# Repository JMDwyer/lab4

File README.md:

# Lab 4: Final Project for ECE 3150
## Team Members: Peter Slater (pas324), Elise Weir (enw23), Joseph Dwyer (jmd456)

### Project Proposal:
>https://docs.google.com/a/cornell.edu/document/d/10tSfkiGi9rwJxMmEFkQvBJDazQcpqDf9e9OWjNXq8RM/edit?usp=sharing

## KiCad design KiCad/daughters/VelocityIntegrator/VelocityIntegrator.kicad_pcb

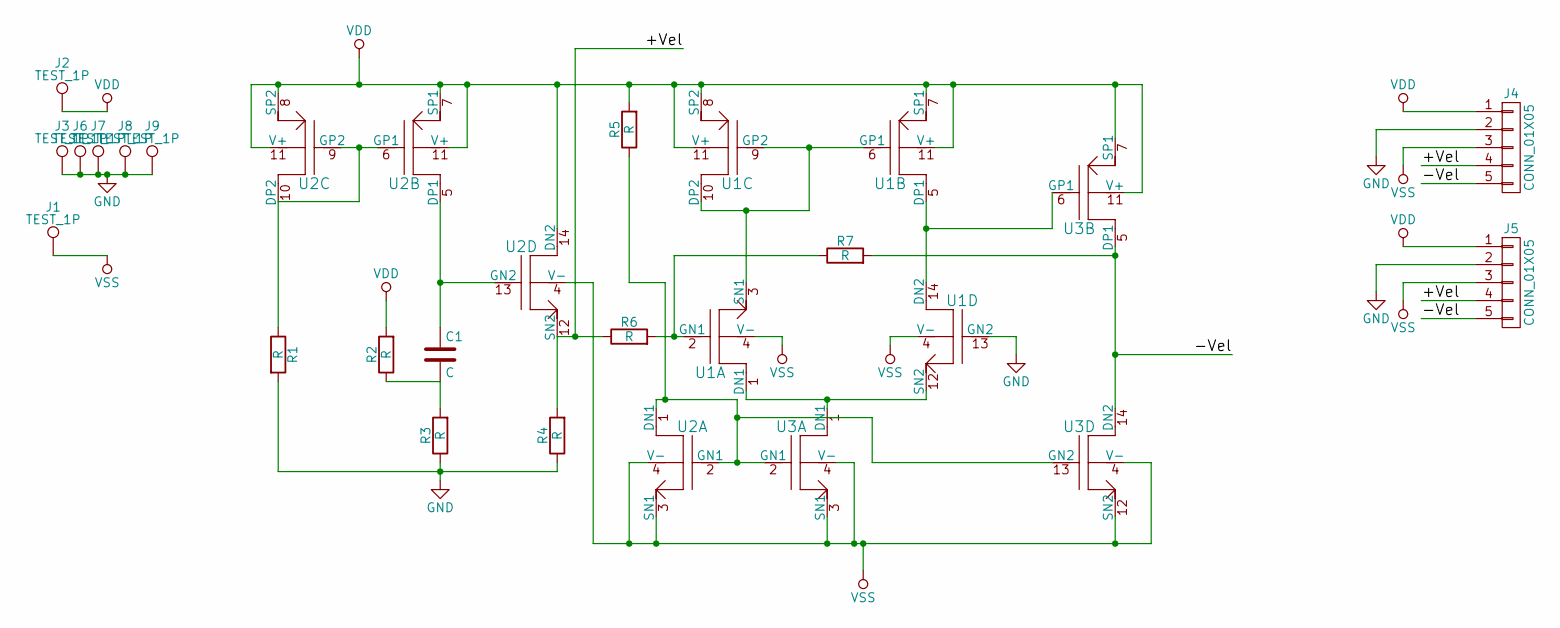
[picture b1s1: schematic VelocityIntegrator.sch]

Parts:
C1: C; CP_Radial_D10.0mm_P5.00mm
J1, J2, J3, J6, J7, J8, J9: TEST_1P; Test_Point
J4, J5: CONN_01X05; Pin_Header_Straight_1x05_Pitch2.54mm
R1, R2, R3, R4, R5, R6, R7: R; R_Axial_DIN0204_L3.6mm_D1.6mm_P5.08mm_Vertical
U1, U2, U3: ALD1105; DIP-14_W7.62mm_LongPads

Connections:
/+Vel: J4.4, J5.4, R4.2, R6.1, U2.12 (SN2)
/-Vel: J4.5, J5.5, R7.2, U3.5 (DP1), U3.14 (DN2)
GND: J3.1, J4.2, J5.2, J6.1, J7.1, J8.1, J9.1, R1.2, R3.1, R4.1, U1.13 (GN2)
unnamed: C1.1, U2.5 (DP1), U2.13 (GN2)
unnamed: C1.2, R2.1, R3.2
unnamed: R1.1, U2.6 (GP1), U2.9 (GP2), U2.10 (DP2)
unnamed: R5.1, U2.1 (DN1), U2.2 (GN1), U3.2 (GN1), U3.13 (GN2)
unnamed: R6.2, R7.1, U1.2 (GN1)
unnamed: U1.1 (DN1), U1.12 (SN2), U3.1 (DN1)
unnamed: U1.3 (SN1), U1.6 (GP1), U1.9 (GP2), U1.10 (DP2)
unnamed: U1.5 (DP1), U1.14 (DN2), U3.6 (GP1)
VDD: J2.1, J4.1, J5.1, R2.2, R5.2, U1.7 (SP1), U1.8 (SP2), U1.11 (V+), U2.7 (SP1), U2.8 (SP2), U2.11 (V+), U2.14 (DN2), U3.7 (SP1), U3.11 (V+)
VSS: J1.1, J4.3, J5.3, U1.4 (V-), U2.3 (SN1), U2.4 (V-), U3.3 (SN1), U3.4 (V-), U3.12 (SN2)

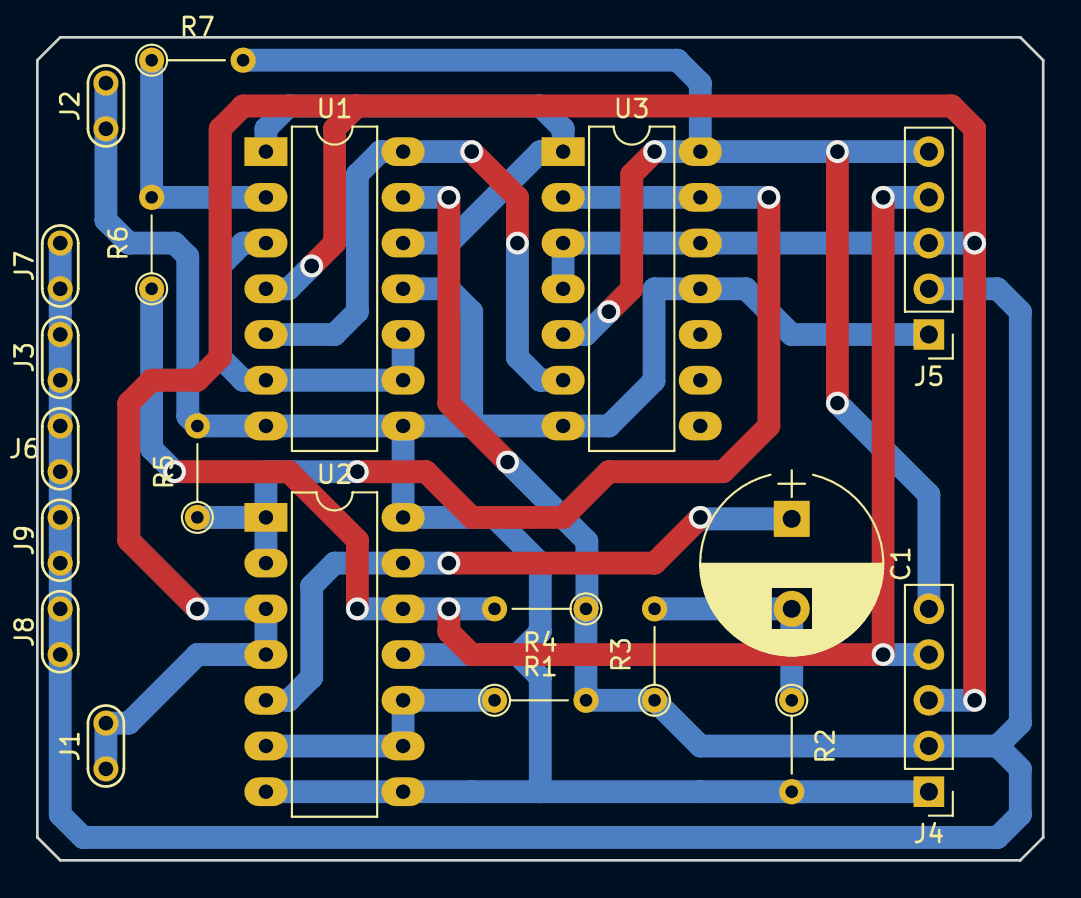
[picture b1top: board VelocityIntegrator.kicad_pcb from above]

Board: 2 copper layers, 55.9 x 45.7 mm, 20 parts (0 on the bottom side), 13 nets.

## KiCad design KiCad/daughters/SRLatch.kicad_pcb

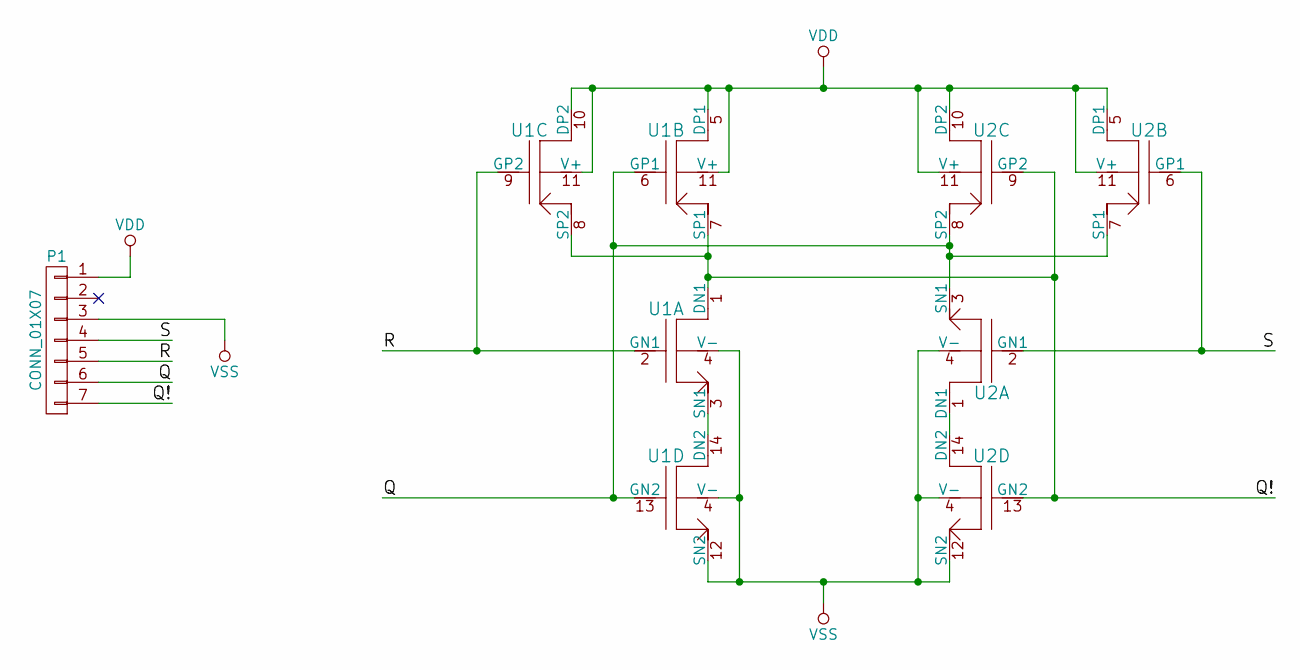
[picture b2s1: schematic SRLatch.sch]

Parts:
P1: CONN_01X07; Pin_Header_Straight_1x07_Pitch2.54mm
U1, U2: ALD1105; DIP-14_W7.62mm_LongPads

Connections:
/Q: P1.6, U1.6 (GP1), U1.13 (GN2), U2.3 (SN1), U2.7 (SP1), U2.8 (SP2)
/Q!: P1.7, U1.1 (DN1), U1.7 (SP1), U1.8 (SP2), U2.9 (GP2), U2.13 (GN2)
/R: P1.5, U1.2 (GN1), U1.9 (GP2)
/S: P1.4, U2.2 (GN1), U2.6 (GP1)
unnamed: U1.3 (SN1), U1.14 (DN2)
unnamed: U2.1 (DN1), U2.14 (DN2)
VDD: P1.1, U1.5 (DP1), U1.10 (DP2), U1.11 (V+), U2.5 (DP1), U2.10 (DP2), U2.11 (V+)
VSS: P1.3, U1.4 (V-), U1.12 (SN2), U2.4 (V-), U2.12 (SN2)

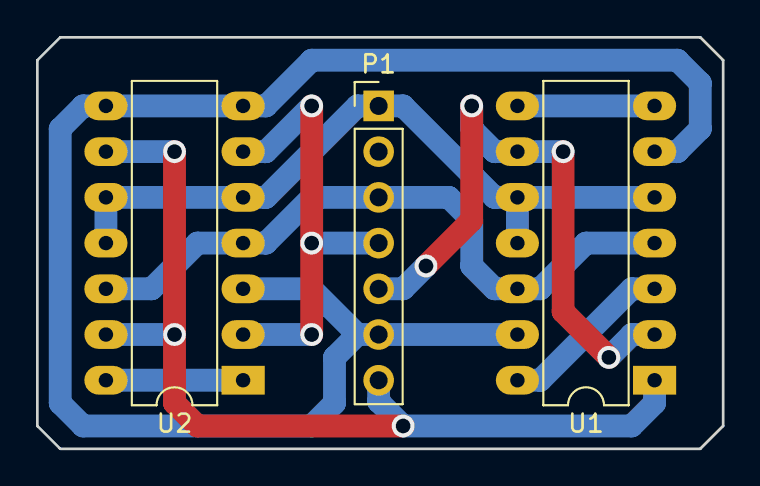
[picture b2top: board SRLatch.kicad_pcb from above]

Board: 2 copper layers, 38.1 x 22.9 mm, 3 parts (0 on the bottom side), 8 nets.

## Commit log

2017-04-23 Add files via upload
    uploaded op amp model
2017-04-23 Add files via upload
    Uploaded contents of zip for easy access
2017-04-24 Reorganized the File structure and added simulink and sources.
2017-04-24 Added SPICE mosfet model source
2017-04-24 added useful parameters document
2017-04-24 Added More Sources
2017-04-24 Fixed typos.
2017-04-30 Add files via upload
    Working Op Amp LT Spice Simulation
    Changes include fixing CD orientation with M10, disconnecting gate and source for M9, eliminating NFET current mirror, and switching out a PFET for an NFET with transistor M10.
2017-05-01 Got 2D simulation working
2017-05-02 Elise - LTSpice Op Amp Model Changes: Added NFET CD Amplifier
2017-05-02 Added Opamp design to axis, tested SR latch operation and made PDF outputs
2017-05-02 added example circuit outputs
2017-05-04 Added some board files and library
